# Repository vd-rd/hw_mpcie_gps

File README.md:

## Hardware Repo for GPS Module 

Open Hardware Mini PCI Express GPS module for embedded telemetry or DIY projects.
The module can be used with both passive and active antennas, supports various GPS modules in the widely used uBlox NEO footprint and is easy to assemble at home.
Check the releases section for Gerber files and updated BOM.

### Resources
You can find all necesary information to build or evaluate the module here:
   - [View layout and schematic](https://cadlab.io/project/1666) 
   - [View 3D board render](https://a360.co/2FOFA9d)
   - [Firmware and libraries](https://github.com/vd-rd/fw_mpcie_gps)
   - [Fabrication files](https://github.com/vd-rd/hw_mpcie_gps/releases)

### Module Features
   * compatible with multiple GPS modules (tested with Fibocom GTS-4E and uBLOX NEO-M6)
   * compliant with the half mPCI Express mechanical and electrical specifications (rev 2.1)
   * relatively easy to assemble at home (some experience with SMD soldering required)
   * no special driver required under Linux (exposed as CDC interface)
   * separate .1inch breakout header for UART interfacing
   * compliant with most cheap mPCI to USB solutions

### System architecture
The GPS receiver architecture consists of a receiver for different constellations (GNSS, Beidou, Glonass, GPS) and a microcontroller for interfacing with the mPCIe bus.

The module expects a +3V3 input capable of sustaining at least 100mA peak currents. Typical consumption is ~20mA for active positioning and reporting and <1mA for sleep state.
The STM32F042 microcontroller is used as a USB to UART bidirectional bridge for converting the data from the GPS module to the USB signals required by the mPCI port and for advanced control over the GPS module.

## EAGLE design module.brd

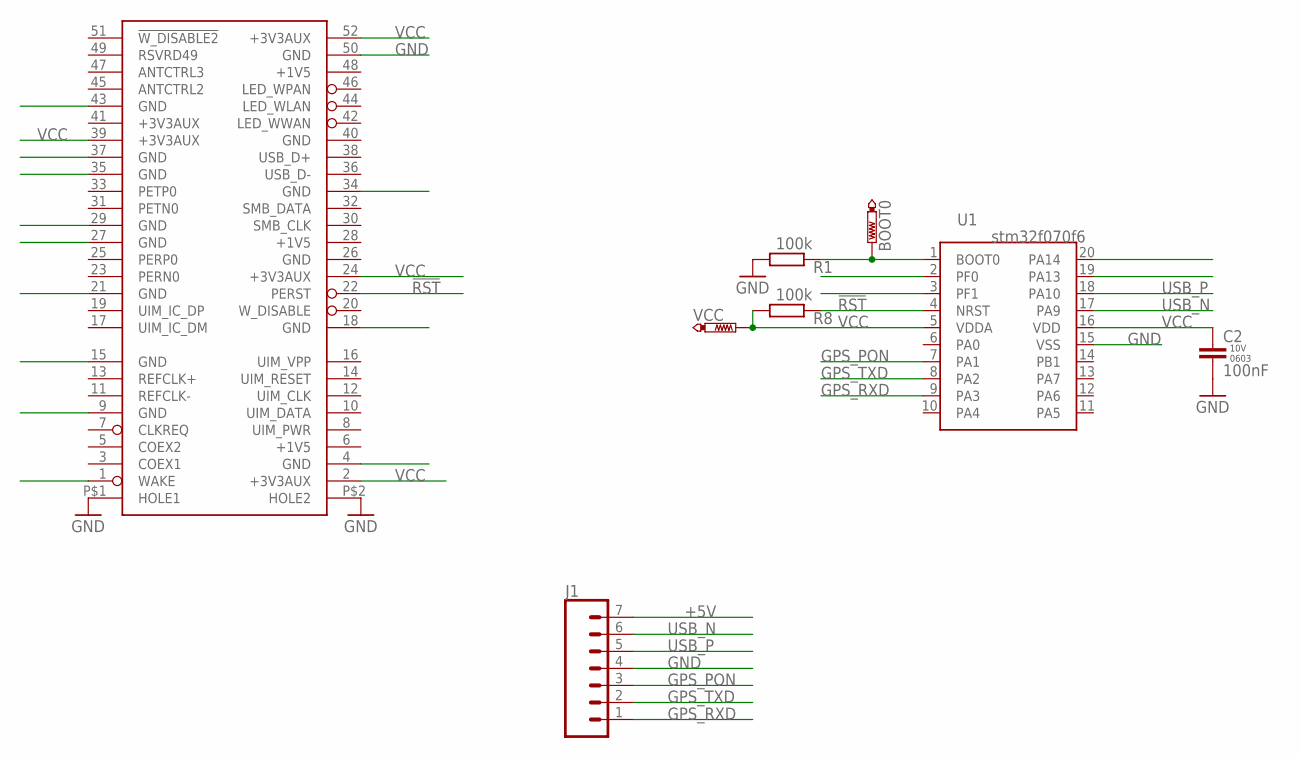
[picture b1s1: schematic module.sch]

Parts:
BOOT0: PTR1B1,27; B1,27
C2: 100nF; C0603
FORM1: MPCIE_HALF
J1: CONN_07; 1X07
R1, R8: 100k; R0603
U1: STM32F070F6; SOP65P640X120-20
VCC: PTR1B1,27; B1,27

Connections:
!RST: FORM1.22 (PERST), R8.1, U1.4 (NRST)
+1V5: FORM1.6 (+1V5), FORM1.28 (+1V5)
+5V: J1.7
GND: C2.2, FORM1.4 (GND), FORM1.9 (GND), FORM1.15 (GND), FORM1.18 (GND), FORM1.21 (GND), FORM1.26 (GND), FORM1.27 (GND), FORM1.29 (GND), FORM1.34 (GND), FORM1.35 (GND), FORM1.37 (GND), FORM1.43 (GND), FORM1.50 (GND), FORM1.P$1 (HOLE1), FORM1.P$2 (HOLE2), J1.4, R1.2, U1.15 (VSS)
GPS_PON: J1.3, U1.7 (PA1)
GPS_RXD: J1.1, U1.9 (PA3)
GPS_TXD: J1.2, U1.8 (PA2)
unnamed: BOOT0.TP, R1.1, U1.1 (BOOT0)
SMB_DATA: FORM1.32 (SMB_DATA)
USB_D+: FORM1.38 (USB_D+)
USB_N: J1.6, U1.17 (PA9)
USB_P: J1.5, U1.18 (PA10)
VCC: C2.1, FORM1.2 (+3V3AUX), FORM1.24 (+3V3AUX), FORM1.39 (+3V3AUX), FORM1.52 (+3V3AUX), R8.2, U1.5 (VDDA), U1.16 (VDD), VCC.TP

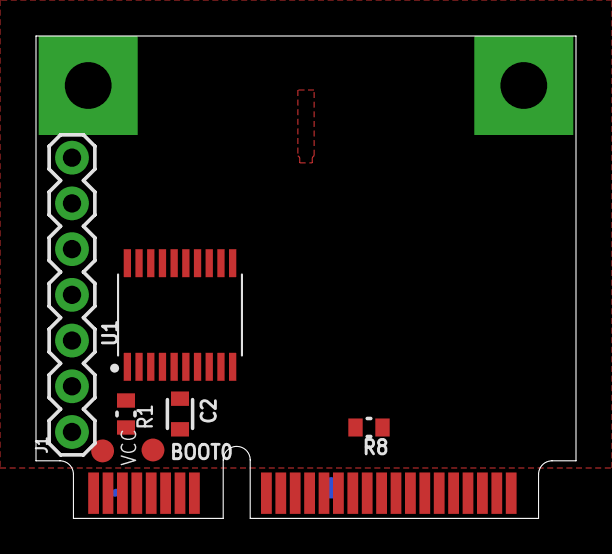
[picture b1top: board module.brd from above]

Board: 2 copper layers, 30.0 x 26.8 mm, 8 parts (0 on the bottom side), 10 nets.

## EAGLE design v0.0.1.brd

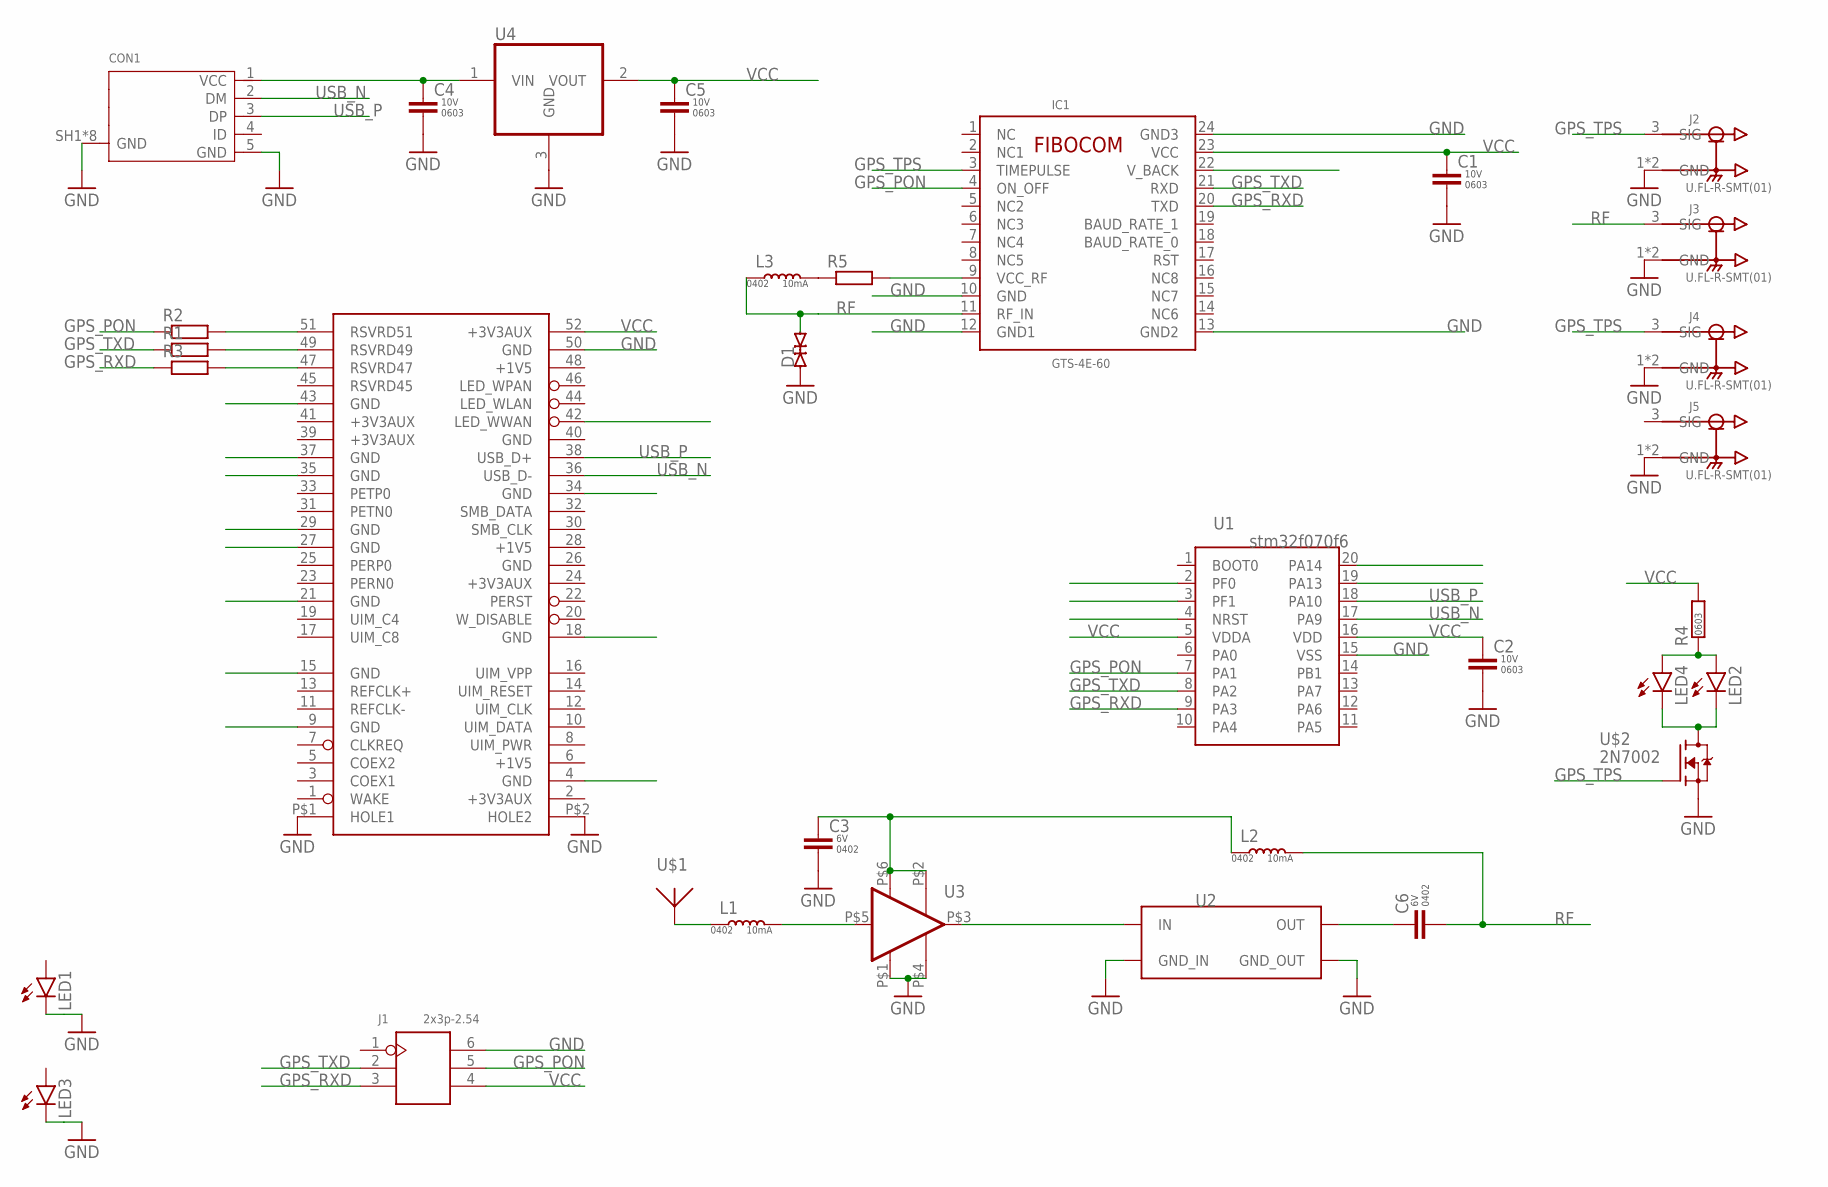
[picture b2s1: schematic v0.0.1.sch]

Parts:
C1, C2, C4, C5: CAP-0603; C0603
C3, C6: CAP-0402; C0402K
CON1: 10118194-0001LF; 10118194
D1: ESD9B5.0ST5G; SOD1006X40
FORM1: MPCIE
IC1: GTS-4E-60; _GTS_4E_60
J1: 2x3p-2.54; H2X3-2.54
J2, J3, J4, J5: U.FL-R-SMT(01); HRS_U.FL-R-SMT(01)
L1, L2, L3: IND-0402; L0402
LED1, LED2, LED3, LED4: LEDCHIP-LED0805; CHIP-LED0805
R1, R2, R3, R5: R-EU_R0402; R0402
R4: RES-0603; R0603
U1: STM32F070F6; SOP65P640X120-20
U2: B3916B8813P810; XSON5
U3: BGU8019; XSON6
U4: AP7333-33SAG-7; SOT95P240X110-3
U$1: ANT1590-2540A; 2540A
U$2: 2N7002; SOT95P240X110-3

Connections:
+1V5: FORM1.6 (+1V5), FORM1.28 (+1V5)
+3V3AUX: FORM1.2 (+3V3AUX), FORM1.24 (+3V3AUX)
GND: C1.2, C2.2, C3.2, C4.2, C5.2, CON1.5 (GND), CON1.SH1 (GND), CON1.SH2 (GND), CON1.SH3 (GND), CON1.SH4 (GND), CON1.SH5 (GND), CON1.SH6 (GND), CON1.SH7 (GND), CON1.SH8 (GND), D1.1 (A), FORM1.4 (GND), FORM1.9 (GND), FORM1.15 (GND), FORM1.18 (GND), FORM1.21 (GND), FORM1.26 (GND), FORM1.27 (GND), FORM1.29 (GND), FORM1.34 (GND), FORM1.35 (GND), FORM1.37 (GND), FORM1.43 (GND), FORM1.50 (GND), FORM1.P$1 (HOLE1), FORM1.P$2 (HOLE2), IC1.10 (GND), IC1.12 (GND1), IC1.13 (GND2), IC1.24 (GND3), J1.6, J2.1 (GND), J2.2 (GND), J3.1 (GND), J3.2 (GND), J4.1 (GND), J4.2 (GND), J5.1 (GND), J5.2 (GND), LED1.C, LED3.C, U1.15 (VSS), U2.2 (GND_IN), U2.3 (GND_OUT), U2.5 (GND_IN), U3.P$1 (GND), U3.P$4 (GND_RF), U4.3 (GND), U$2.2 (S)
GPS_PON: IC1.4 (ON_OFF), J1.5, R2.1, U1.7 (PA1)
GPS_RXD: IC1.20 (TXD), J1.3, R3.1, U1.9 (PA3)
GPS_TPS: IC1.3 (TIMEPULSE), J2.3 (SIG), J4.3 (SIG), U$2.1 (G)
GPS_TXD: IC1.21 (RXD), J1.2, R1.1, U1.8 (PA2)
unnamed: FORM1.51 (RSVRD51), R2.2
unnamed: FORM1.49 (RSVRD49), R1.2
unnamed: FORM1.47 (RSVRD47), R3.2
unnamed: L1.1, U$1.P$1
unnamed: L1.2, U3.P$5 (RF_IN)
unnamed: U2.1 (IN), U3.P$3 (RF_OUT)
unnamed: C3.1, L2.1, U3.P$2 (VCC), U3.P$6 (ENABLE)
unnamed: C6.1, U2.4 (OUT)
unnamed: LED2.C, LED4.C, U$2.3 (D)
unnamed: LED2.A, LED4.A, R4.1
unnamed: C4.1, CON1.1 (VCC), U4.1 (VIN)
unnamed: IC1.9 (VCC_RF), R5.2
unnamed: L3.2, R5.1
RF: C6.2, D1.2 (C), IC1.11 (RF_IN), J3.3 (SIG), L2.2, L3.1
SMB_DATA: FORM1.32 (SMB_DATA)
USB_N: CON1.2 (DM), FORM1.36 (USB_D-), U1.17 (PA9)
USB_P: CON1.3 (DP), FORM1.38 (USB_D+), U1.18 (PA10)
VCC: C1.1, C2.1, C5.1, FORM1.52 (+3V3AUX), IC1.23 (VCC), J1.4, R4.2, U1.5 (VDDA), U1.16 (VDD), U4.2 (VOUT)

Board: 2 copper layers, 33 parts (1 on the bottom side), 24 nets, no tracks yet.

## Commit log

2019-02-06 board floorplan
2019-04-01 added board renders
2019-04-01 Backlink to CADLAB.io has been added.
2019-04-02 added updated files
2019-04-02 add open hardware license
2019-09-16 project: clear the way for a new revision
2022-01-19 Revert "add open hardware license"
    This reverts commit c871bbf4ff330b0a4173ed04cb87fa7ae3c9c24a.

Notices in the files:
parts and their libraries:
SparkFun-Connectors: Licensing: Creative Commons ShareAlike 4.0 International - https://creativecommons.org/licenses/by-sa/4.0
